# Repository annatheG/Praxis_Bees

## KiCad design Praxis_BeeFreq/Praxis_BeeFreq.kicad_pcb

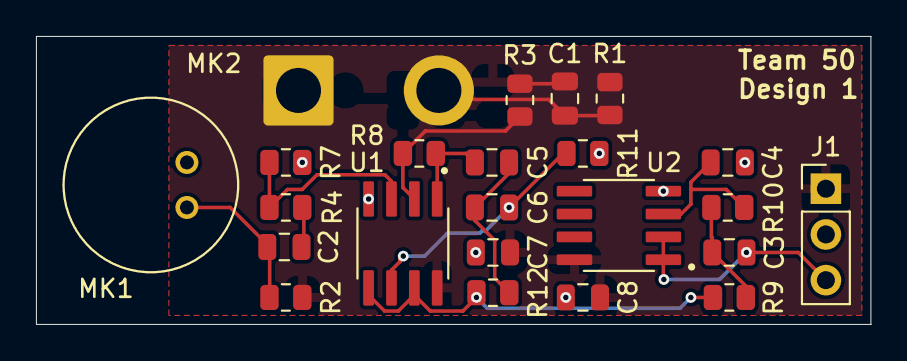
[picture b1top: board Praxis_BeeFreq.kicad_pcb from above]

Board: 2 copper layers, 46.4 x 16.0 mm, 23 parts (0 on the bottom side), 15 nets.

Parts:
C1, C2: 1u; C_0805_2012Metric
C3: 20n; C_0805_2012Metric
C4: 11n; C_0805_2012Metric
C5, C6: 10n; C_0805_2012Metric
C7, C8: 100nF; C_0805_2012Metric
J1: Conn_01x03_Pin; PinHeader_1x03_P2.54mm_Vertical
MK1: CMA-6542PF; CUI_CMA-6542PF
MK2: CMA-6542PF; SolderWire-2sqmm_1x02_P7.8mm_D2mm_OD3.9mm
R1, R2: 2.2k; R_0805_2012Metric
R3, R4, R7, R8: 100; R_0805_2012Metric
R9, R10: 20k; R_0805_2012Metric
R11: 150k; R_0805_2012Metric
R12: 68k; R_0805_2012Metric
U1, U2: NE5532DR; SOIC127P599X175-8N

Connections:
/output: C3.2, J1.3, U2.1 (1OUT), U2.2 (1IN-)
GND: C4.2, C7.2, C8.2, J1.2, MK1.GND, MK2.1, R7.2, R11.2, U1.4 (VCC-), U2.4 (VCC-)
unnamed: C1.1, MK2.2, R1.2
unnamed: C1.2, R3.1
unnamed: C2.1, MK1.OUT, R2.2
unnamed: C2.2, R4.1
unnamed: C3.1, R9.1, R10.2
unnamed: C5.2, C6.1, R12.1
unnamed: R4.2, R7.1, U1.3 (1IN+)
unnamed: R3.2, R8.1, U1.2 (1IN-)
unnamed: C5.1, R8.2, U1.1 (1OUT)
unnamed: C6.2, R11.1, U1.6 (2IN+)
unnamed: R9.2, R12.2, U1.5 (2IN-), U1.7 (2OUT)
unnamed: C4.1, R10.1, U2.3 (1IN+)
VCC: C7.1, C8.1, J1.1, R1.1, R2.1, U1.8 (VCC+), U2.8 (VCC+)

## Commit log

2025-03-31 KiCad
2025-03-31 ConnectorFix
2025-03-31 BetterVersion
